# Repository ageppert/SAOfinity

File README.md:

# SAOfinity

An SAO display solution, with options!

-------------

# V1.0 First Draft - Shared at Hackaday Supercon.9 in 2025

The SAO DEMO CONTROLLER is available for purchase here: https://www.tindie.com/products/36033/

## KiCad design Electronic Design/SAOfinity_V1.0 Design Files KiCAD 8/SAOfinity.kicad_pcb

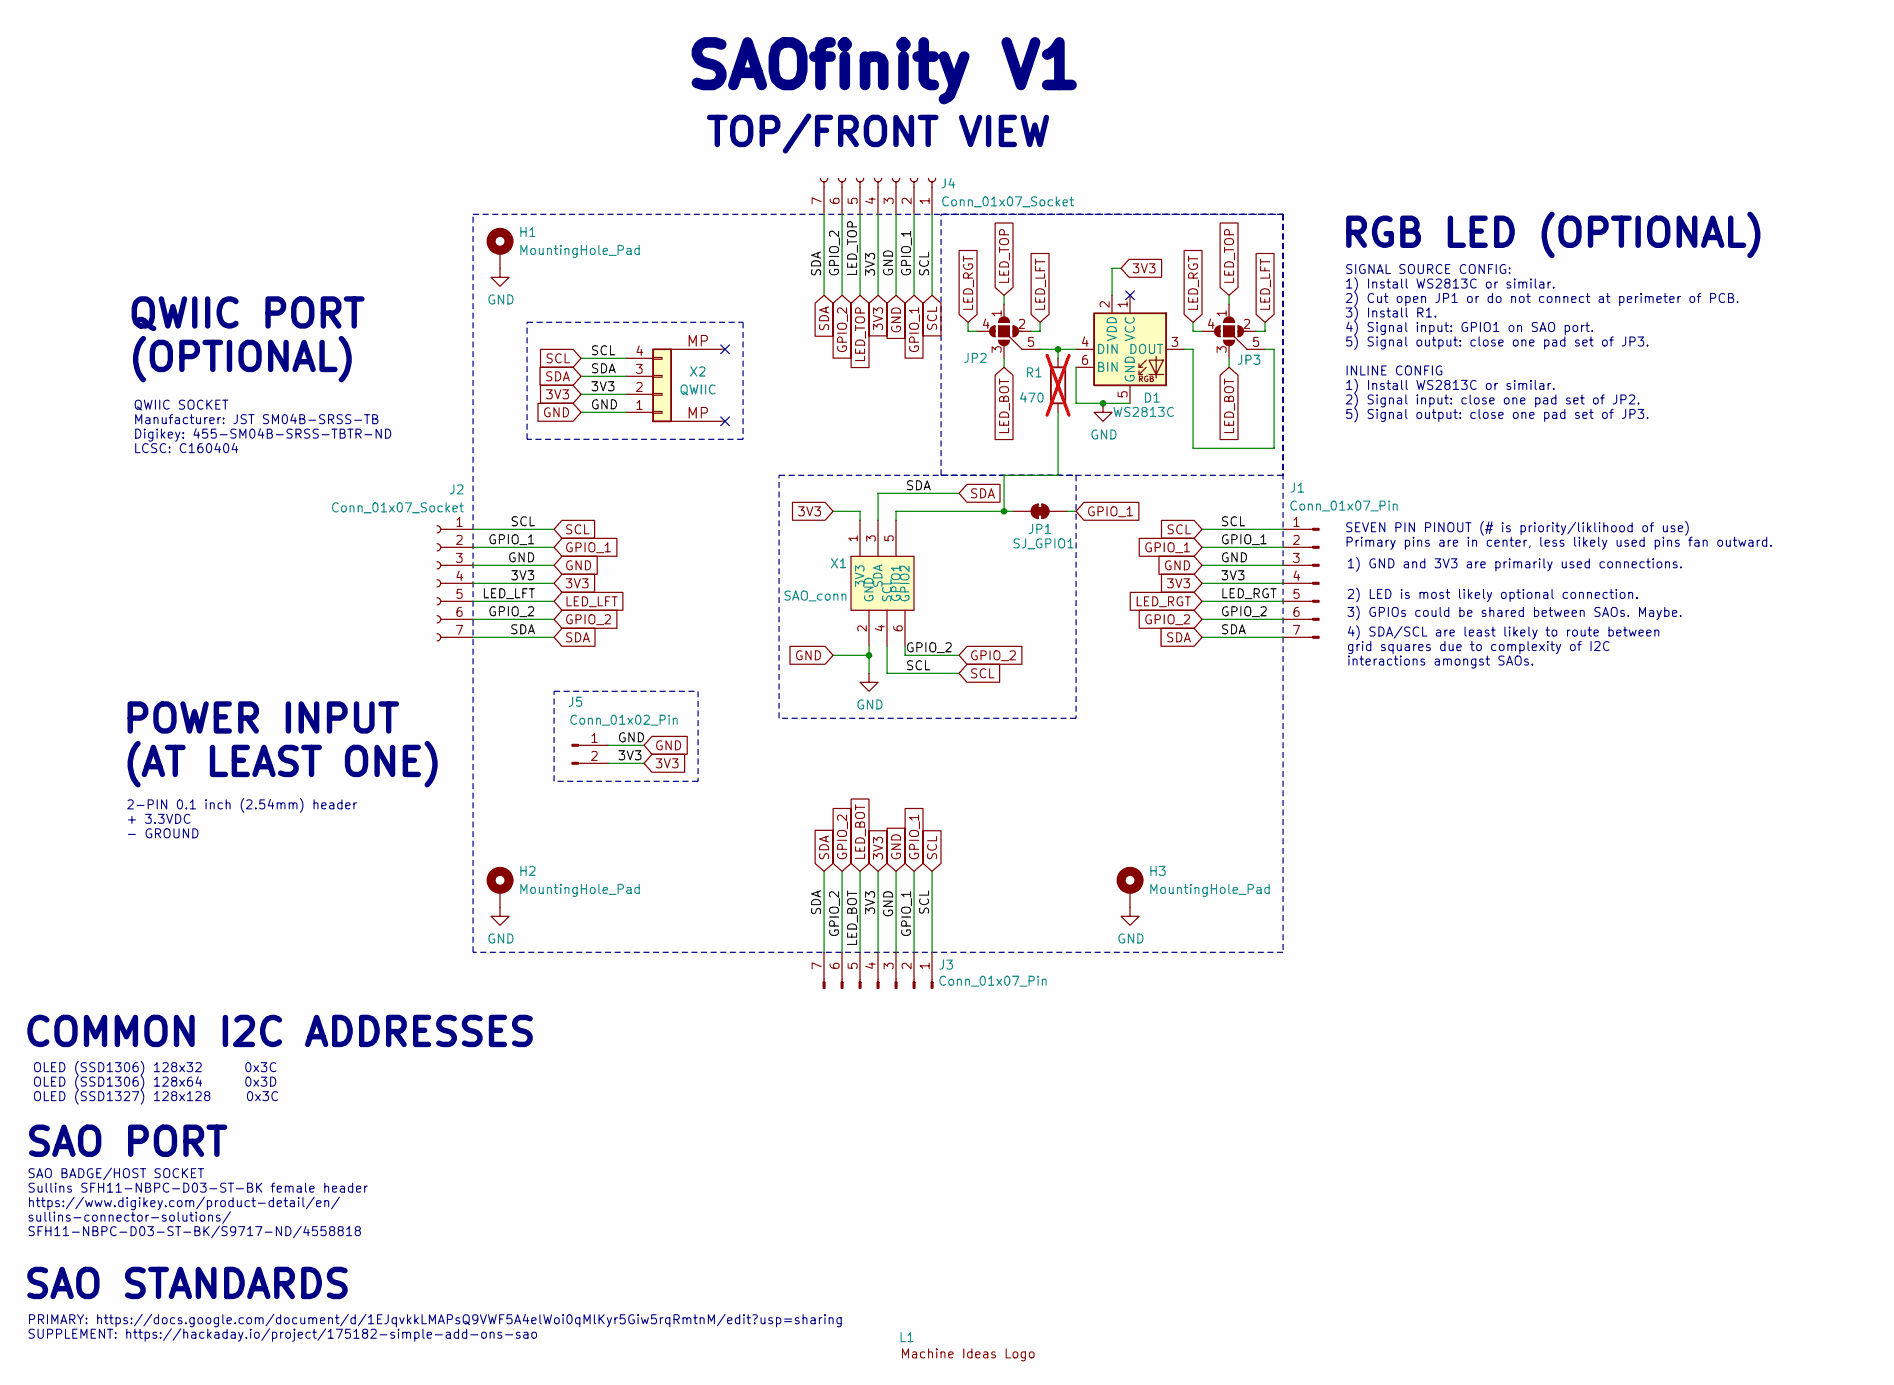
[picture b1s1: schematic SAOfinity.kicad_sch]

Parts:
D1: WS2813C; LED_WS2813_PLCC6_5.0x5.0mm_P1.6mm_Core64_Abg_Mod; JLCPCB P/N C5359034
H1, H2, H3: MountingHole_Pad; TestPoint_THTPad_D1.5mm_Drill1.0mm
J1, J3: Conn_01x07_Pin; PinHeader_1x07_P2.54mm_Horizontal
J2, J4: Conn_01x07_Socket; PinSocket_1x07_P2.54mm_Horizontal
J5: Conn_01x02_Pin; PinSocket_1x02_P2.54mm_Vertical
JP1: SJ_GPIO1; SolderJumper-2_P1.3mm_Bridged_RoundedPad1.0x1.5mm
JP2, JP3: SolderJumper_5_Open; SolderJumper-5_P1.3mm_Open_RoundedPad1.0x1.5mm_NumberLabels
L1: Machine_Ideas_logo
R1: 470; R_0805_2012Metric; LCSC C17710; not fitted
X1: SAO_conn; Badgelife-SAOv169-BADGE-2x3-no-front-text-yes-front-outline; MPN SFH11-NBPC-D03-ST-BK
X2: QWIIC; JST_SH_SM04B-SRSS-TB_1x04-1MP_P1.00mm_Horizontal; MPN SM04B-SRSS-TB; LCSC C160404

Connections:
3V3: D1.2 (VDD), J1.4, J2.4, J3.4, J4.4, J5.2, X1.1 (3V3), X2.2
GND: D1.5 (GND), D1.6 (BIN), H1.1, H2.1, H3.1, J1.3, J2.3, J3.3, J4.3, J5.1, X1.2 (GND), X2.1
GPIO_1: J1.2, J2.2, J3.2, J4.2, JP1.2 (B)
GPIO_2: J1.6, J2.6, J3.6, J4.6, X1.6 (GPIO2)
LED_BOT: J3.5, JP2.3 (C), JP3.3 (C)
LED_LFT: J2.5, JP2.2 (B), JP3.2 (B)
LED_RGT: J1.5, JP2.4 (D), JP3.4 (D)
LED_TOP: J4.5, JP2.1 (A), JP3.1 (A)
unnamed: D1.4 (DIN), JP2.5 (E), R1.2
unnamed: D1.3 (DOUT), JP3.5 (E)
unnamed: JP1.1 (A), R1.1, X1.5 (GPIO1)
SCL: J1.1, J2.1, J3.1, J4.1, X1.4 (SCL), X2.4
SDA: J1.7, J2.7, J3.7, J4.7, X1.3 (SDA), X2.3

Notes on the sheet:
RGB LED (OPTIONAL)
SAO BADGE/HOST SOCKET Sullins SFH11-NBPC-D03-ST-BK female header https://www.digikey.com/product-detail/en/ sullins-connector-solutions/ SFH11-NBPC-D03-ST-BK/S9717-ND/4558818
COMMON I2C ADDRESSES
QWIIC SOCKET Manufacturer: JST SM04B-SRSS-TB Digikey: 455-SM04B-SRSS-TBTR-ND LCSC: C160404
3) GPIOs could be shared between SAOs. Maybe.
2) LED is most likely optional connection.
4) SDA/SCL are least likely to route between grid squares due to complexity of I2C interactions amongst SAOs.
POWER INPUT (AT LEAST ONE)
OLED (SSD1306) 128x32 0x3C OLED (SSD1306) 128x64 0x3D OLED (SSD1327) 128x128 0x3C
SEVEN PIN PINOUT (# is priority/liklihood of use) Primary pins are in center, less likely used pins fan outward.
SAO STANDARDS
PRIMARY: https://docs.google.com/document/d/1EJqvkkLMAPsQ9VWF5A4elWoi0qMlKyr5Giw5rqRmtnM/edit?usp=sharing SUPPLEMENT: https://hackaday.io/project/175182-simple-add-ons-sao
TOP/FRONT VIEW
QWIIC PORT (OPTIONAL)
1) GND and 3V3 are primarily used connections.
2-PIN 0.1 inch (2.54mm) header + 3.3VDC - GROUND
SAO PORT
SIGNAL SOURCE CONFIG: 1) Install WS2813C or similar. 2) Cut open JP1 or do not connect at perimeter of PCB. 3) Install R1. 4) Signal input: GPIO1 on SAO port. 5) Signal output: close one pad set of JP3. INLINE CONFIG 1) Install WS2813C or similar. 2) Signal input: close one pad set of JP2. 5) Signa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
SAOfinity V1

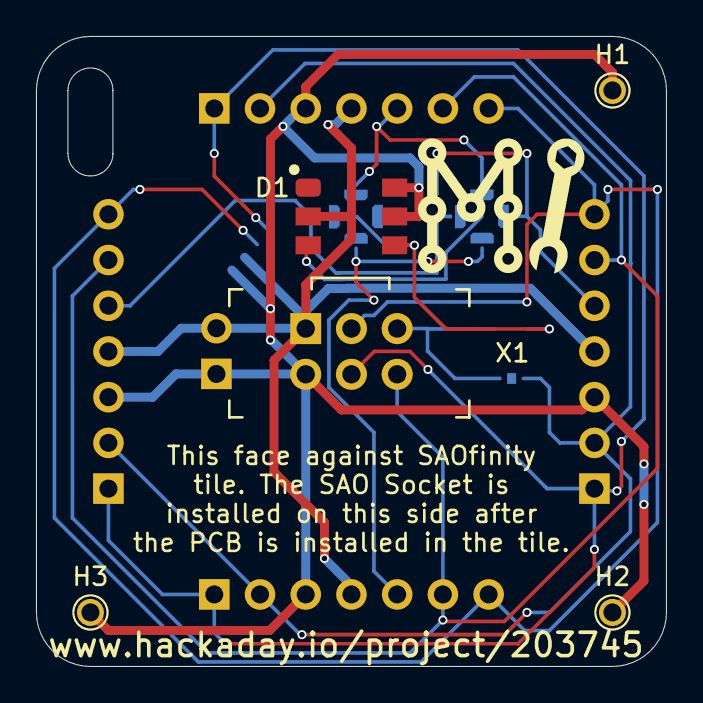
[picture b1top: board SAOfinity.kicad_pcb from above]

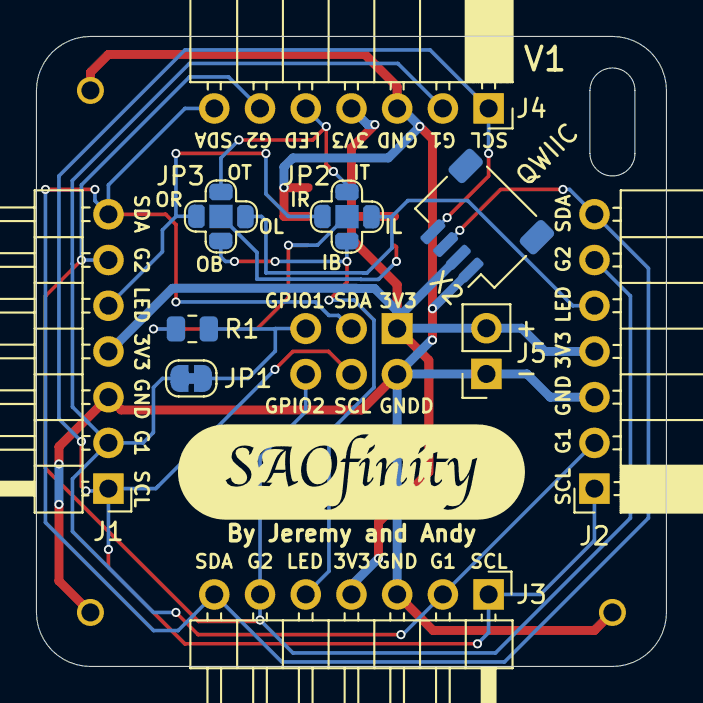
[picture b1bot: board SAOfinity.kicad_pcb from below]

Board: 2 copper layers, 35.0 x 35.0 mm, 17 parts (11 on the bottom side), 13 nets.

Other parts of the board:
kibuzzard-68D4AC2E: G***; kibuzzard-68D4AC2E

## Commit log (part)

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2025-09-27 Initial release with V1 files
2025-09-29 Add LED Datasheet
2025-10-27 Add demo code based on Adafruit's "strandtest_nodelay" configured for 36 tiles
